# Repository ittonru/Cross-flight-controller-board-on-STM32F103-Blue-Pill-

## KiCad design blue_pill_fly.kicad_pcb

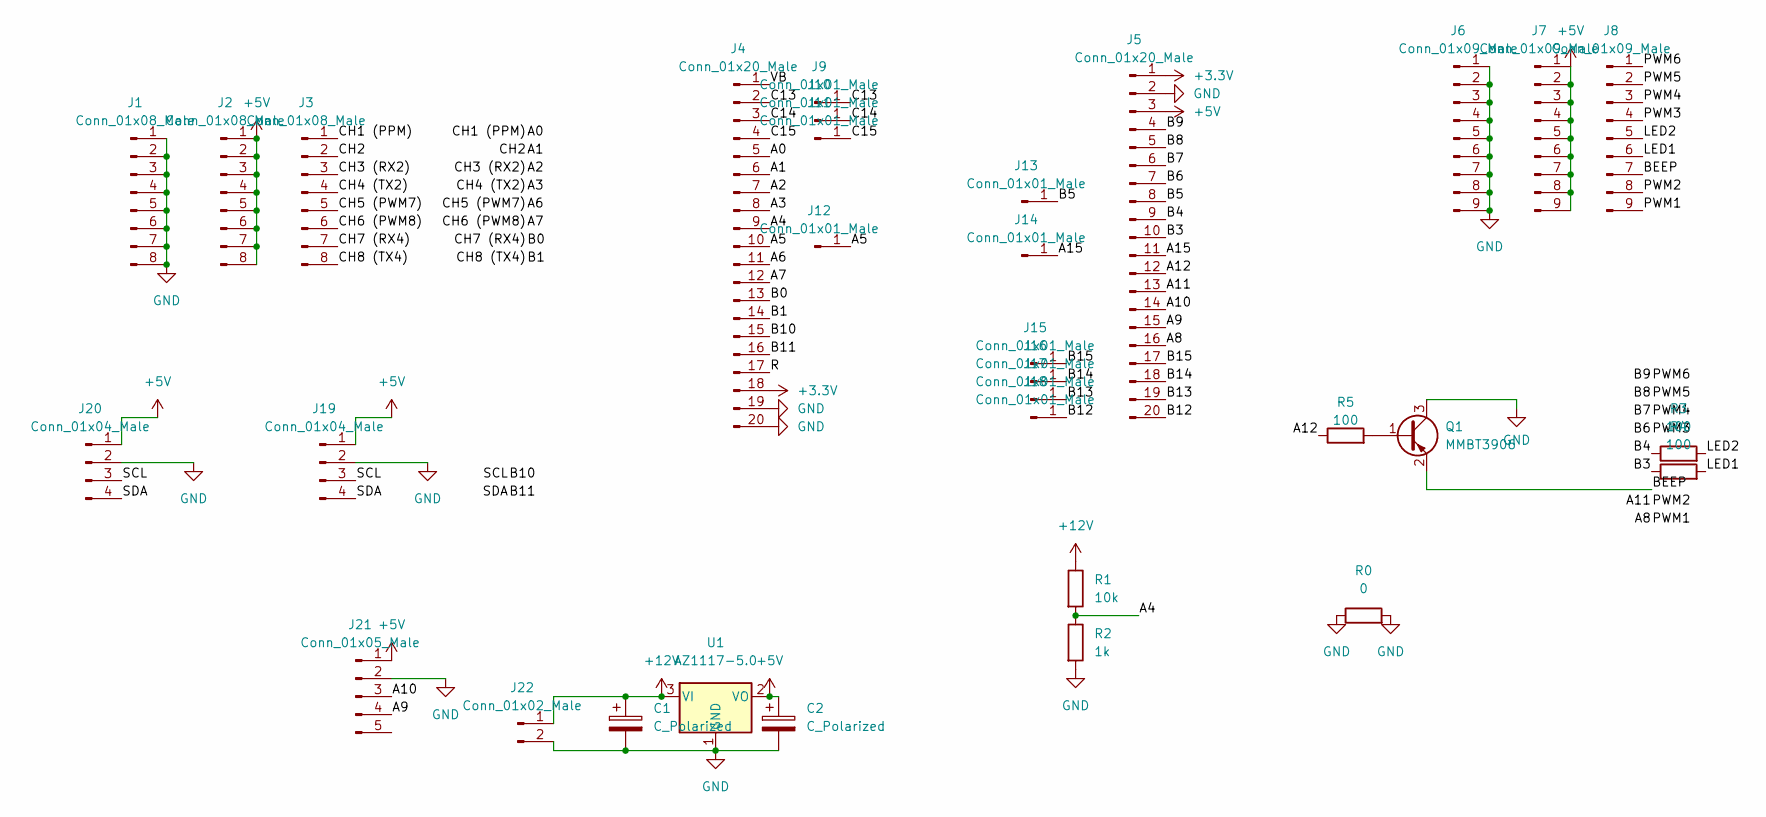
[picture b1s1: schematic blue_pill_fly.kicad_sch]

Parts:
C1, C2: C_Polarized; CP_EIA-6032-15_Kemet-U
J1, J2, J3: Conn_01x08_Male; PinHeader_1x08_P2.54mm_Vertical
J4, J5: Conn_01x20_Male; PinHeader_1x20_P2.54mm_Vertical
J6, J7, J8: Conn_01x09_Male; PinHeader_1x09_P2.54mm_Vertical
J9, J10, J11, J12, J13, J14, J15, J16, J17, J18: Conn_01x01_Male; PinHeader_1x01_P2.54mm_Vertical
J19, J20: Conn_01x04_Male; PinHeader_1x04_P2.54mm_Vertical
J21: Conn_01x05_Male; PinHeader_1x05_P2.54mm_Vertical
J22: Conn_01x02_Male; PinHeader_1x02_P2.54mm_Vertical
Q1: MMBT3906; SOT-23
R0: 0; R_1206_3216Metric
R1: 10k; R_Axial_DIN0207_L6.3mm_D2.5mm_P7.62mm_Horizontal
R2: 1k; R_Axial_DIN0207_L6.3mm_D2.5mm_P7.62mm_Horizontal
R3, R4, R5: 100; R_0603_1608Metric
U1: AZ1117-5.0; SOT-223-3_TabPin2

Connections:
+3V3: J4.18, J5.1
+5V: C2.1, J2.1, J2.2, J2.3, J2.4, J2.5, J2.6, J2.7, J2.8, J5.3, J7.1, J7.2, J7.3, J7.4, J7.5, J7.6, J7.7, J7.8, J7.9, J19.1, J20.1, J21.1, U1.2 (VO)
+12V: C1.1, J22.1, R1.1, U1.3 (VI)
/A0: J3.1, J4.5
/A1: J3.2, J4.6
/A2: J3.3, J4.7
/A3: J3.4, J4.8
/A4: J4.9, R1.2, R2.1
/A5: J4.10, J12.1
/A6: J3.5, J4.11
/A7: J3.6, J4.12
/A8: J5.16, J8.9
/A9: J5.15, J21.4
/A10: J5.14, J21.3
/A11: J5.13, J8.8
/A12: J5.12, R5.1
/A15: J5.11, J14.1
/B0: J3.7, J4.13
/B1: J3.8, J4.14
/B3: J5.10, R4.1
/B4: J5.9, R3.1
/B5: J5.8, J13.1
/B6: J5.7, J8.4
/B7: J5.6, J8.3
/B8: J5.5, J8.2
/B9: J5.4, J8.1
/B10: J4.15, J19.3, J20.3
/B11: J4.16, J19.4, J20.4
/B12: J5.20, J18.1
/B13: J5.19, J17.1
/B14: J5.18, J16.1
/B15: J5.17, J15.1
/BEEP: J8.7, Q1.2 (E)
/C13: J4.2, J9.1
/C14: J4.3, J10.1
/C15: J4.4, J11.1
/LED1: J8.6, R4.2
/LED2: J8.5, R3.2
/R: J4.17
/VB: J4.1
GND: C1.2, C2.2, J1.1, J1.2, J1.3, J1.4, J1.5, J1.6, J1.7, J1.8, J4.19, J4.20, J5.2, J6.1, J6.2, J6.3, J6.4, J6.5, J6.6, J6.7, J6.8, J6.9, J19.2, J20.2, J21.2, J22.2, Q1.3 (C), R0.1, R0.2, R2.2, U1.1 (GND)
unnamed: Q1.1 (B), R5.2

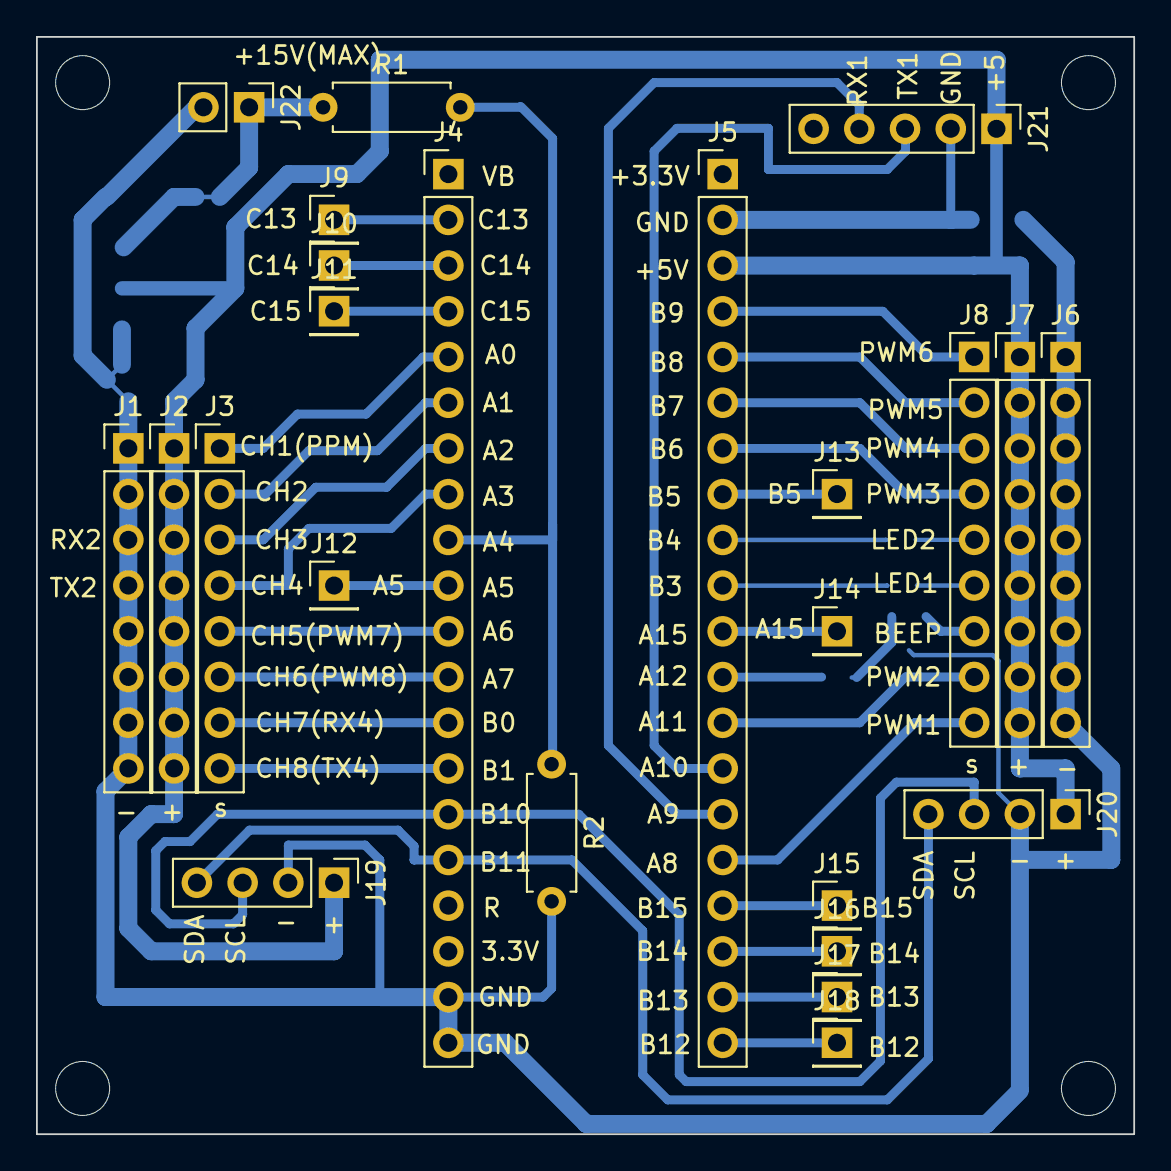
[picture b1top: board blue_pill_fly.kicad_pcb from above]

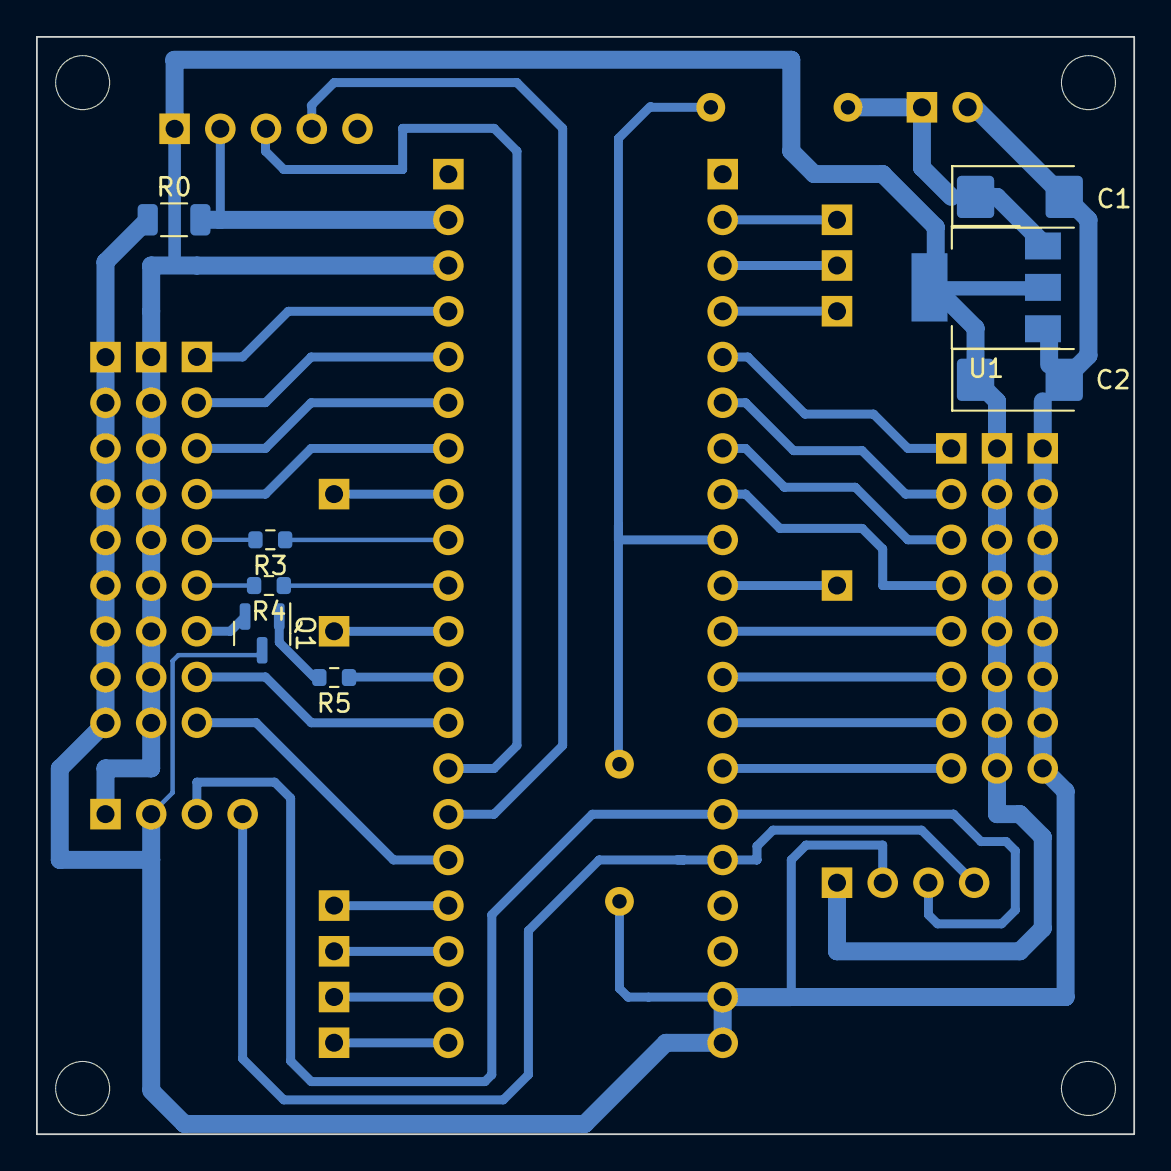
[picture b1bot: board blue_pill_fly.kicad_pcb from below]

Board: 2 copper layers, 61.0 x 61.0 mm, 36 parts (8 on the bottom side), 40 nets.

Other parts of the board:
0, 0#2, 0#3, 0#4: .; hole_3_2
